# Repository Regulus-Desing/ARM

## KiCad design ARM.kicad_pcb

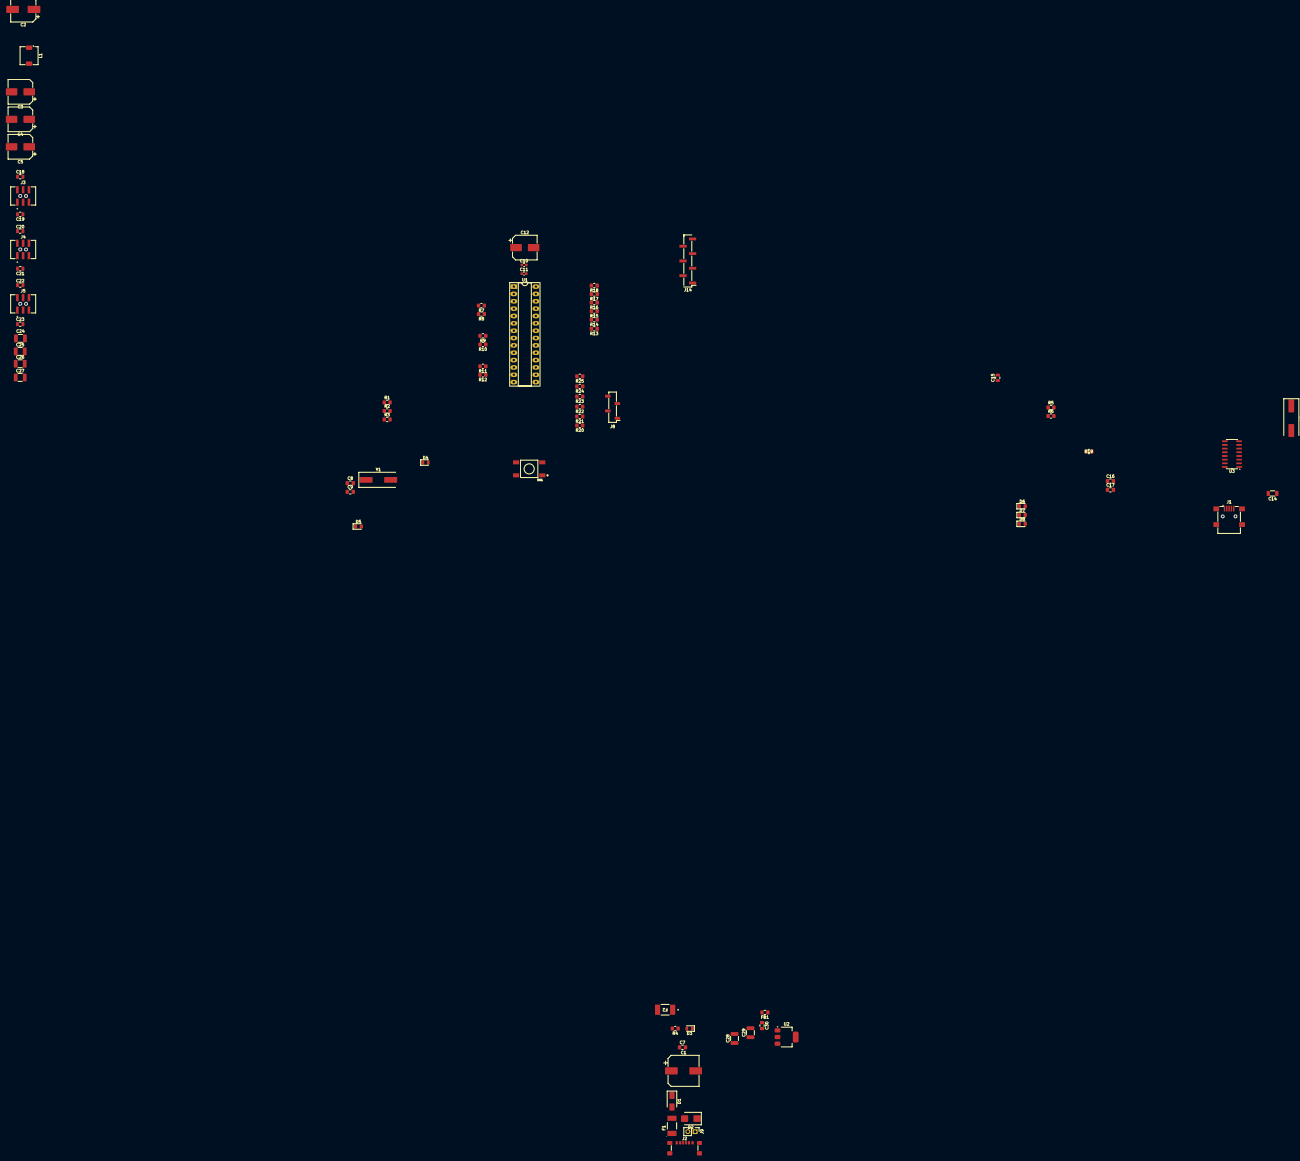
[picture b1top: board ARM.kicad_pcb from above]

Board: 2 copper layers, 79 parts (0 on the bottom side), 56 nets, no tracks yet.

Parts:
C1: 2200µF 25v baja ESR; CP_Elec_10x10.5
C2: 4.7UF 16v; CP_Elec_8x10.5
C3, C4, C5: 470UF 16V baja ESR; CP_Elec_8x6.2
C7: 100nF 16v; C_0805_2012Metric_Pad1.18x1.45mm_HandSolder
C8, C9, C16, C17: 22pF 16v; C_0805_2012Metric_Pad1.18x1.45mm_HandSolder
C10, C11: 0.1UF 16v; C_0603_1608Metric
C12: 47µF 16v; CP_Elec_8x6.2
C14: 10µF 16v; C_1206_3216Metric
C15: 0.1 µF 16v; C_0805_2012Metric
C18, C19, C20, C21, C22, C23: 100NF; C_0805_2012Metric
C24: 1UF-16V; C_1210_3225Metric_Pad1.33x2.70mm_HandSolder
C25: 4,7UF-16V; C_1210_3225Metric_Pad1.33x2.70mm_HandSolder
C26, C28, C29: 10UF-16V; C_1210_3225Metric_Pad1.33x2.70mm_HandSolder
C27: 22UF-16V; C_1210_3225Metric_Pad1.33x2.70mm_HandSolder
C30: 0.1µF 16V; C_0805_2012Metric_Pad1.18x1.45mm_HandSolder
D1: SS14; D_SMA
D2: D_TVS 9V SMBJ12A; D_SMB
D3: LED Red; LED_0805_2012Metric
D4: LED Green; LED_0805_2012Metric
D5: LED Blue; LED_0805_2012Metric_Pad1.15x1.40mm_HandSolder
D6: LED White; LED_0805_2012Metric_Pad1.15x1.40mm_HandSolder
D7: LED Yellow; LED_0805_2012Metric_Pad1.15x1.40mm_HandSolder
D8: LED Orange; LED_0805_2012Metric_Pad1.15x1.40mm_HandSolder
F1: 1812L110_24DR; FUSM4632X200N
F2: PTS18126V300; FUSE_PTS18126_COB
FB1: Ferrite 100MHz 600Ω 2A; L_0805_2012Metric_Pad1.15x1.40mm_HandSolder
J1: USB_OTG; USB_Mini-B_Lumberg_2486_01_Horizontal
J2: USB_C_Receptacle_PowerOnly_6P +5v; USB_C_Receptacle_GCT_USB4135-GF-A_6P_TopMnt_Horizontal
J3, J4, J5: G823MB06221KYEU; AMPHENOL_G823MB06221KYEU
J8: Conn_01x04_Socket; PinSocket_1x04_P2.54mm_Vertical_SMD_Pin1Left
J9: Conn_01x02_Socket; PinHeader_1x02_P2.54mm_Vertical
J14: Conn_01x07_Socket; PinHeader_1x07_P2.54mm_Vertical_SMD_Pin1Left
L1: L_Small; L_TDK_SLF6045
R1, R22, R25: 10 kΩ 1%; R_0805_2012Metric_Pad1.20x1.40mm_HandSolder
R2, R3, R4, R5, R6, R19: 330Ω 1%; R_0805_2012Metric_Pad1.20x1.40mm_HandSolder
R7, R8, R9, R10, R11, R12: 220Ω 1%; R_0805_2012Metric_Pad1.20x1.40mm_HandSolder
R13, R14, R15, R16, R17, R18: 10KΩ 1%; R_0805_2012Metric_Pad1.20x1.40mm_HandSolder
R20, R21, R23, R24: 33Ω 1%; R_0805_2012Metric_Pad1.20x1.40mm_HandSolder
SW1: 4-1437565-9; TE_4-1437565-9
U1: ATMEGA328-PU; DIP-28_W7.62mm_Socket_LongPads
U2: AMS1117-3.3v; SOT-223-3_TabPin2
U3: CH340G; SOIC-16_3.9x9.9mm_P1.27mm
Y1: Crystal 20Mhz; Crystal_SMD_HC49-SD
Y2: 12Mhz; Crystal_SMD_HC49-SD

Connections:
3,3v: C30.1, FB1.2, J14.7
+5vE: F1.1, J2.A9 (VBUS), J2.B9 (VBUS), J9.2
+5v_Micro: C1.1, C7.1, C10.1, C11.1, C12.1, C14.1, C15.1, C28.1, D1.1 (K), F2.1, J1.1 (VBUS), R1.1, R4.2, R5.2, R22.1, R25.1, U1.7 (VCC), U1.20 (AVCC), U2.3 (VI), U3.16 (VCC)
GND: C1.2, C2.2, C3.2, C4.2, C5.2, C7.2, C8.2, C9.1, C10.2, C11.2, C12.2, C14.2, C15.2, C16.1, C17.1, C18.1, C19.2, C20.2, C21.2, C22.2, C23.1, C24.2, C25.1, C26.1, C27.1, C28.2, C29.2, C30.2, D2.1 (A1), D3.1 (K), D4.1 (K), D5.1 (K), D6.1 (K), D7.1 (K), D8.1 (K), J1.5 (GND), J1.6 (Shield), J2.A12 (GND), J2.B12 (GND), J2.S1 (SHIELD), J3.1, J3.2, J4.1, J4.2, J5.1, J5.2, J9.1, SW1.1, SW1.2, U1.8 (GND), U1.22 (GND__1), U2.1 (GND), U3.1 (GND)
ISP1: J8.1, R20.1
ISP2: J8.2, R21.1
ISP3: J8.3, R23.1
ISP4: J8.4, R24.1
unnamed: D1.2 (A), D2.2 (A2), F1.2
unnamed: D3.2 (A), R4.1
unnamed: D4.2 (A), R3.1
unnamed: D5.2 (A), R2.1
unnamed: D6.2 (A), R5.1
unnamed: D7.2 (A), R6.1
unnamed: D8.2 (A), R19.1
unnamed: J1.3 (D+), U3.5 (UD+)
unnamed: J1.2 (D-), U3.6 (UD-)
unnamed: J14.1, R13.2
unnamed: J14.2, R14.2
unnamed: J14.3, R15.2
unnamed: J14.4, R16.2
unnamed: J14.5, R17.2
unnamed: J14.6, R18.2
unnamed: R3.2, U1.14 (PB0(PCINT0/CLKO/ICP1))
unnamed: R2.2, U1.15 (PB1(OC1A/PCINT1))
unnamed: R24.2, R25.2, U1.16 (PB2(~SS/OC1B/PCINT2))
unnamed: R20.2, U1.17 (PB3(MOSI/OC2A/PCINT3))
unnamed: R21.2, R22.2, U1.18 (PB4(MISO/PCINT4))
unnamed: R23.2, U1.19 (PB5(SCK/PCINT5))
unnamed: C9.2, U1.9 (PB6(PCINT6/XTAL1/TOSC1)), Y1.1
unnamed: C8.1, U1.10 (PB7(PCINT7/XTAL2/TOSC2)), Y1.2
unnamed: R13.1, U1.23 (PC0(ADC0/PCINT8))
unnamed: R14.1, U1.24 (PC1(ADC1/PCINT9))
unnamed: R15.1, U1.25 (PC2(ADC2/PCINT10))
unnamed: R16.1, U1.26 (PC3(ADC3/PCINT11))
unnamed: R17.1, U1.27 (PC4(ADC4/SDA/PCINT12))
unnamed: R18.1, U1.28 (PC5(ADC5/SCL/PCINT13))
unnamed: R1.2, SW1.3, SW1.4, U1.1 (PC6(PCINT14/~RESET))
unnamed: R7.1, U1.4 (PD2(PCINT18/INT0))
unnamed: R8.1, U1.5 (PD3(PCINT19/OC2B/INT1))
unnamed: R9.1, U1.6 (PD4(PCINT20/XCK/T0))
unnamed: R10.1, U1.11 (PD5(PCINT21/OC0B/T1))
unnamed: R11.1, U1.12 (PD6(PCINT22/OC0A/AIN0))
unnamed: R12.1, U1.13 (PD7(PCINT23/AIN1))
unnamed: C29.1, FB1.1, U2.2 (VO)
unnamed: C16.2, U3.7 (XI), Y2.2
unnamed: C17.2, U3.8 (XO), Y2.1
S1: J3.6, R7.2
S2: J3.5, R8.2
S3: J4.6, R9.2
S4: J4.5, R10.2
S5: J5.6, R11.2
S6: J5.5, R12.2
USB_RX: R6.2, U1.2 (PD0(PCINT16/RXD)), U3.2 (TXD)
USB_TX: R19.2, U1.3 (PD1(PCINT17/TXD)), U3.3 (RXD)
V5_SERVOS_PRE_L1: C2.1, C3.1, C4.1, C5.1, C18.2, C19.1, C20.1, C21.1, C22.1, C23.2, C24.1, C25.2, C26.2, C27.2, F2.2, J3.3, J3.4, J4.3, J4.4, J5.3, J5.4, L1.1, L1.2

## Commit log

2025-09-04 Add files via upload
    Project: Robotic Arm with ATmega328PB
    Description
    This project implements a 6-degree-of-freedom robotic arm using an ATmega328PB-AU microcontroller as the control unit.
    The design includes a custom PCB, voltage regulation, communication, and servomotor control modules. The goal is to create a robust, fully documented platform ready to be manufactured and assembled b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
    Main Features
    Microcontroller: ATmega328PB-AU (8-bit AVR architecture).
2025-09-19 push files
2025-09-19 mistake
2025-09-19 Revert "mistake"
    This reverts commit 8728f3de92bb642d3a5581e7387178a88eb5d2a4.
